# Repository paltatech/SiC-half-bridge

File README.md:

# SiC-half-bridge
Three parallel SiC(Silicon Carbide) Mosfet half bridge

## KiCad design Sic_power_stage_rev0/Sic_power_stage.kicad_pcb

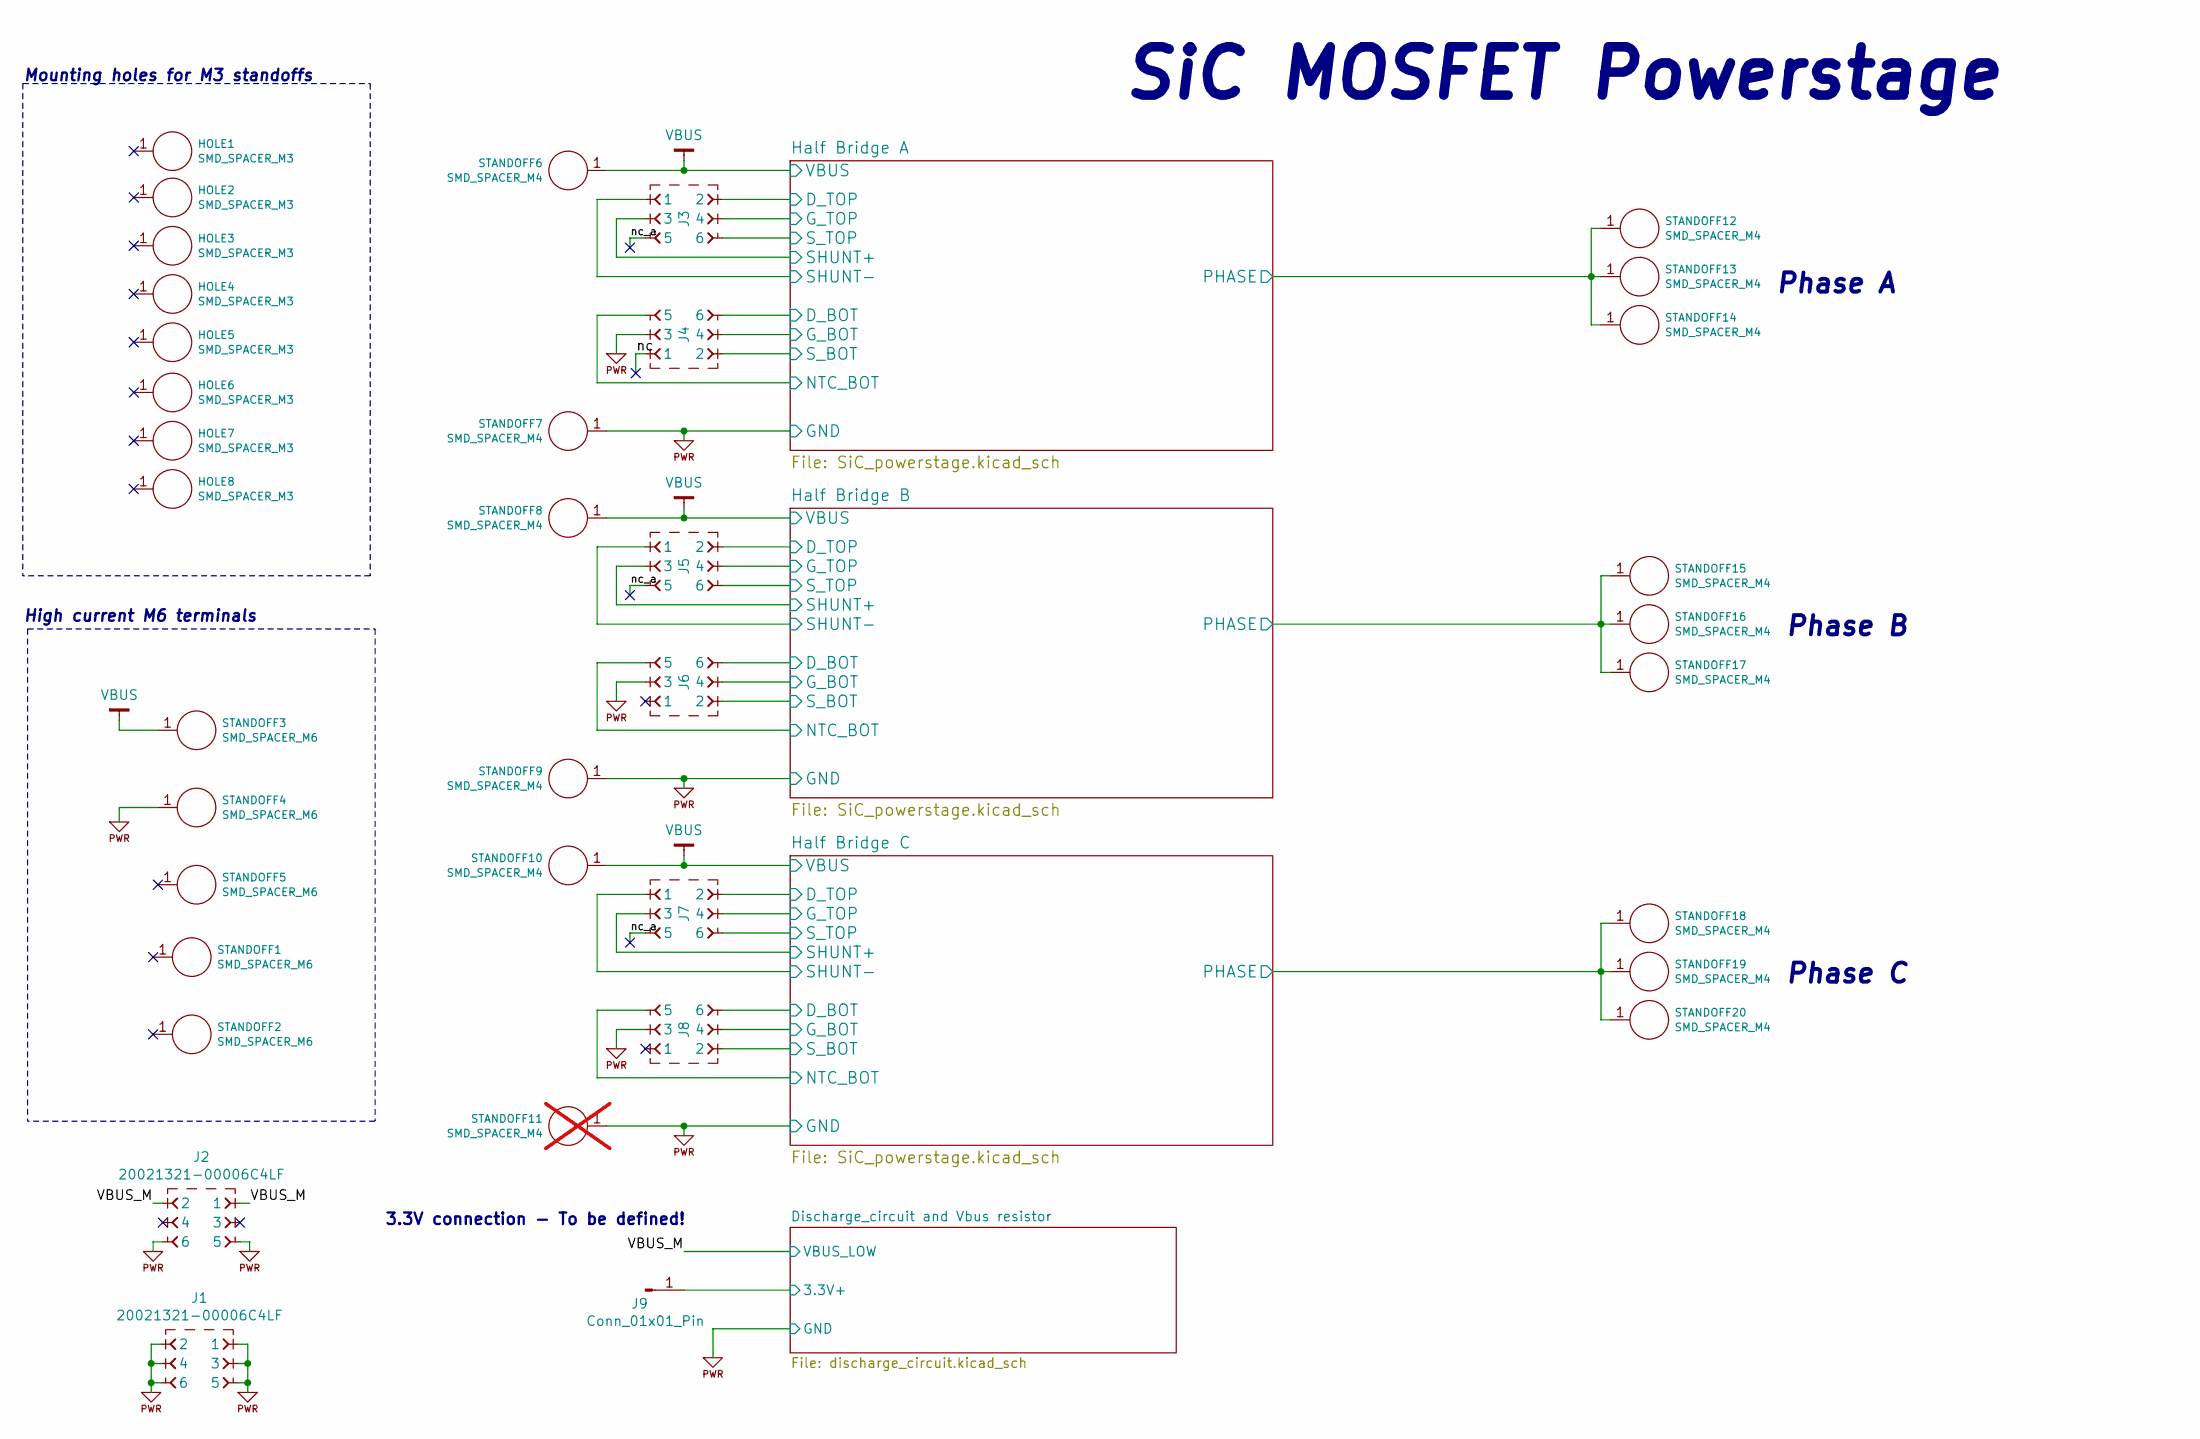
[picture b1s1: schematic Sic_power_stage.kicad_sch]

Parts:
HOLE1, HOLE2, HOLE3, HOLE4, HOLE5, HOLE6, HOLE7, HOLE8: SMD_SPACER_M3; SMTSO-36-6; MPN SMTSO-36-60-MTJ
J1, J2, J3, J4, J5, J6, J7, J8: 20021321-00006C4LF; CONN-20021321-00006C4LF-no-hole; MPN 20021321-00006C4LF
J9: Conn_01x01_Pin; PinHeader_1x01_P1.00mm_Vertical
STANDOFF1, STANDOFF2, STANDOFF3, STANDOFF4, STANDOFF5: SMD_SPACER_M6; Standoff_M4; MPN Brass Inserts(M6*8*12)
STANDOFF6, STANDOFF7, STANDOFF8, STANDOFF9, STANDOFF10, STANDOFF12, STANDOFF13, STANDOFF14, STANDOFF15, STANDOFF16, STANDOFF17, STANDOFF18, STANDOFF19, STANDOFF20: SMD_SPACER_M4; Standoff_M4; MPN SMTSO-40-120-M-T-S
STANDOFF11: SMD_SPACER_M4; Standoff_M4; MPN SMTSO-40-120-M-T-S; not fitted

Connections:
/Discharge_circuit and Vbus resistor/3.3V+: J9.1; also elsewhere on the board
/Half Bridge A/D_BOT: J4.6; also elsewhere on the board
/Half Bridge A/D_TOP: J3.2; also elsewhere on the board
/Half Bridge A/G_BOT: J4.4; also elsewhere on the board
/Half Bridge A/G_TOP: J3.4; also elsewhere on the board
/Half Bridge A/NTC_BOT: J4.5; also elsewhere on the board
/Half Bridge A/PHASE: STANDOFF12.1, STANDOFF13.1, STANDOFF14.1; also elsewhere on the board
/Half Bridge A/SHUNT+: J3.3; also elsewhere on the board
/Half Bridge A/SHUNT-: J3.1; also elsewhere on the board
/Half Bridge A/S_BOT: J4.2; also elsewhere on the board
/Half Bridge A/S_TOP: J3.6; also elsewhere on the board
/Half Bridge B/D_BOT: J6.6; also elsewhere on the board
/Half Bridge B/D_TOP: J5.2; also elsewhere on the board
/Half Bridge B/G_BOT: J6.4; also elsewhere on the board
/Half Bridge B/G_TOP: J5.4; also elsewhere on the board
/Half Bridge B/NTC_BOT: J6.5; also elsewhere on the board
/Half Bridge B/PHASE: STANDOFF15.1, STANDOFF16.1, STANDOFF17.1; also elsewhere on the board
/Half Bridge B/SHUNT+: J5.3; also elsewhere on the board
/Half Bridge B/SHUNT-: J5.1; also elsewhere on the board
/Half Bridge B/S_BOT: J6.2; also elsewhere on the board
/Half Bridge B/S_TOP: J5.6; also elsewhere on the board
/Half Bridge C/D_BOT: J8.6; also elsewhere on the board
/Half Bridge C/D_TOP: J7.2; also elsewhere on the board
/Half Bridge C/G_BOT: J8.4; also elsewhere on the board
/Half Bridge C/G_TOP: J7.4; also elsewhere on the board
/Half Bridge C/NTC_BOT: J8.5; also elsewhere on the board
/Half Bridge C/PHASE: STANDOFF18.1, STANDOFF19.1, STANDOFF20.1; also elsewhere on the board
/Half Bridge C/SHUNT+: J7.3; also elsewhere on the board
/Half Bridge C/SHUNT-: J7.1; also elsewhere on the board
/Half Bridge C/S_BOT: J8.2; also elsewhere on the board
/Half Bridge C/S_TOP: J7.6; also elsewhere on the board
/VBUS_M: J2.1, J2.2; also elsewhere on the board
/nc: J4.1
/nc_a: J3.5, J5.5, J7.5
PWRGND: J1.1, J1.2, J1.3, J1.4, J1.5, J1.6, J2.5, J2.6, J4.3, J6.3, J8.3, STANDOFF4.1, STANDOFF7.1, STANDOFF9.1, STANDOFF11.1; also elsewhere on the board
VBUS: STANDOFF3.1, STANDOFF6.1, STANDOFF8.1, STANDOFF10.1; also elsewhere on the board

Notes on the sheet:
High current M6 terminals
Mounting holes for M3 standoffs
Phase B
Phase A
Phase C
3.3V connection - To be defined!
SiC MOSFET Powerstage

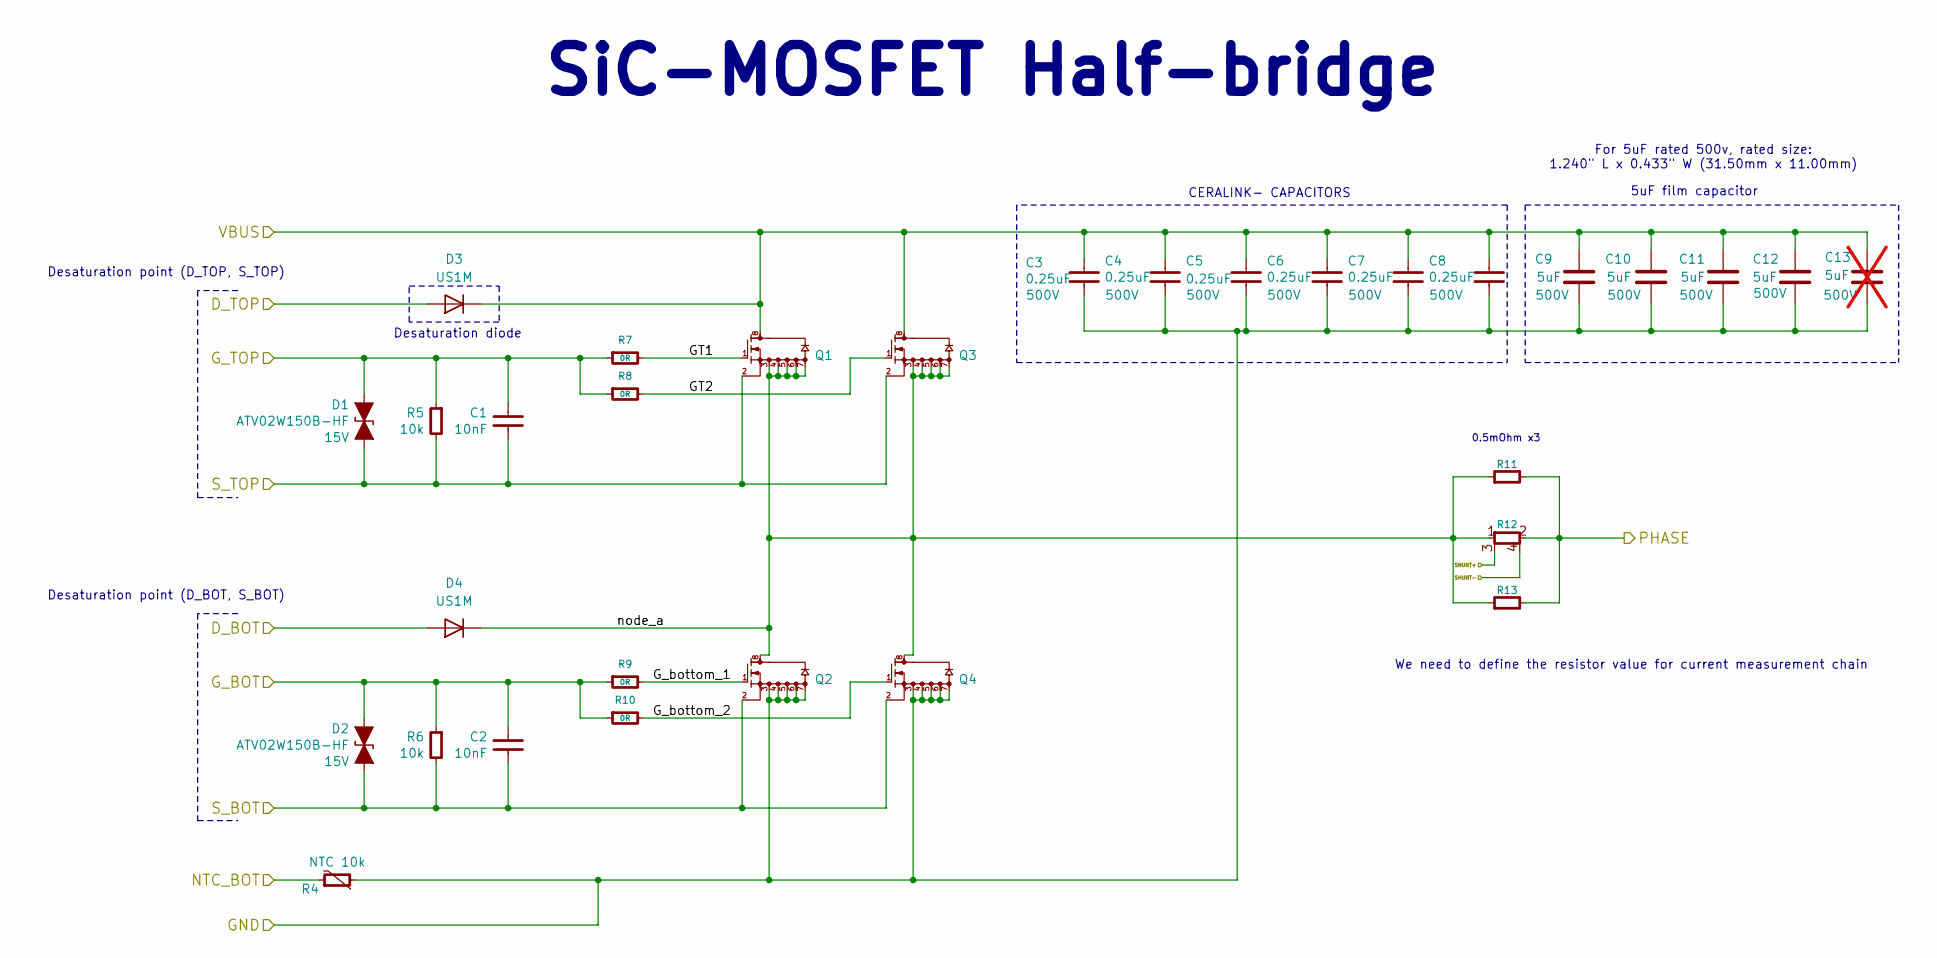
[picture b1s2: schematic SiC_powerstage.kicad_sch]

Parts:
C1, C2: 10nF; CAPC1608X55; Voltage 50V; MPN C1608X7R1H103K080AA
C3: 0.25uF; CAPC5750X279; MPN B58043I5254M052
C4, C5, C6, C7, C8: 0.25uF; CAPC5750X279; Voltage 500V; MPN B58043I5254M052
C9, C10, C11, C12: 5uF; C_Rect_L31.5mm_W11.0mm_P27.50mm_MKS4; Voltage 500V; MPN B32714H5505K000
C13: 5uF; C_Rect_L18.0mm_W9.0mm_P15.00mm_FKS3_FKP3; Voltage 500V; MPN B32714H5505K000; not fitted
D1, D2: ATV02W150B-HF; SOD-123F; Voltage 15V; MPN ATV02W150B-HF
D3, D4: US1M; D_SMA
Q1, Q2, Q3, Q4: NTBG014N120M3P; TO-263-7_TabPin8; MPN NTBG014N120M3P; LCSC Part # C5209029
R4: NTC 10k; RESC1608X50; MPN NCU18XH103F60RB
R5, R6: 10k; RESC1608X50; MPN AC0603FR-0710KL
R7, R8, R9, R10: 0R; RESC1608X50; MPN RMCF0603ZT0R00
R11, R13: 500UOhm; VISHAY-WSL3921L5000FEA; MPN WSLP3921L5000FEA
R12: 500UOhm; WSL3921L5000FEA; MPN WSLP3921L5000FEA

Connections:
/Half Bridge A/D_BOT: D4.2 (A); also elsewhere on the board
/Half Bridge A/D_TOP: D3.2 (A); also elsewhere on the board
/Half Bridge A/GT1: Q1.1, R7.2
/Half Bridge A/GT2: Q3.1, R8.2
/Half Bridge A/G_BOT: C2.1, D2.1 (A1), R6.1, R9.1, R10.1; also elsewhere on the board
/Half Bridge A/G_TOP: C1.1, D1.1 (A1), R5.1, R7.1, R8.1; also elsewhere on the board
/Half Bridge A/G_bottom_1: Q2.1, R9.2
/Half Bridge A/G_bottom_2: Q4.1, R10.2
/Half Bridge A/NTC_BOT: R4.1; also elsewhere on the board
/Half Bridge A/PHASE: R11.2, R12.2, R13.2; also elsewhere on the board
/Half Bridge A/SHUNT+: R12.3; also elsewhere on the board
/Half Bridge A/SHUNT-: R12.4; also elsewhere on the board
/Half Bridge A/S_BOT: C2.2, D2.2 (A2), Q2.2, Q4.2, R6.2; also elsewhere on the board
/Half Bridge A/S_TOP: C1.2, D1.2 (A2), Q1.2, Q3.2, R5.2; also elsewhere on the board
/Half Bridge A/node_a: D4.1 (K), Q1.3, Q1.4, Q1.5, Q1.6, Q1.7, Q2.8, Q3.3, Q3.4, Q3.5, Q3.6, Q3.7, Q4.8, R11.1, R12.1, R13.1
PWRGND: C3.2, C4.2, C5.2, C6.2, C7.2, C8.2, C9.2, C10.2, C11.2, C12.2, C13.2, Q2.3, Q2.4, Q2.5, Q2.6, Q2.7, Q4.3, Q4.4, Q4.5, Q4.6, Q4.7, R4.2; also elsewhere on the board
VBUS: C3.1, C4.1, C5.1, C6.1, C7.1, C8.1, C9.1, C10.1, C11.1, C12.1, C13.1, D3.1 (K), Q1.8, Q3.8; also elsewhere on the board

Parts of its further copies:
C14, C15, C27, C28: 10nF; CAPC1608X55; Voltage 50V; MPN C1608X7R1H103K080AA
C16, C29: 0.25uF; CAPC5750X279; MPN B58043I5254M052
C17, C18, C19, C20, C21, C30, C31, C32, C33, C34: 0.25uF; CAPC5750X279; Voltage 500V; MPN B58043I5254M052
C22, C23, C24, C25, C35, C36, C37, C38: 5uF; C_Rect_L31.5mm_W11.0mm_P27.50mm_MKS4; Voltage 500V; MPN B32714H5505K000
D5, D6, D9, D10: ATV02W150B-HF; SOD-123F; Voltage 15V; MPN ATV02W150B-HF
D7, D8, D11, D12: US1M; D_SMA
Q5, Q6, Q7, Q8, Q9, Q10, Q11, Q12: NTBG014N120M3P; TO-263-7_TabPin8; MPN NTBG014N120M3P; LCSC Part # C5209029
R14, R24: NTC 10k; RESC1608X50; MPN NCU18XH103F60RB
R15, R16, R25, R26: 10k; RESC1608X50; MPN AC0603FR-0710KL
R17, R18, R19, R20, R27, R28, R29, R30: 0R; RESC1608X50; MPN RMCF0603ZT0R00
R21, R23, R31, R33: 500UOhm; VISHAY-WSL3921L5000FEA; MPN WSLP3921L5000FEA
R22, R32: 500UOhm; WSL3921L5000FEA; MPN WSLP3921L5000FEA

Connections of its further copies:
/Half Bridge B/D_BOT: D8.2 (A); also elsewhere on the board
/Half Bridge B/D_TOP: D7.2 (A); also elsewhere on the board
/Half Bridge B/GT1: Q5.1, R17.2
/Half Bridge B/GT2: Q7.1, R18.2
/Half Bridge B/G_BOT: C15.1, D6.1 (A1), R16.1, R19.1, R20.1; also elsewhere on the board
/Half Bridge B/G_TOP: C14.1, D5.1 (A1), R15.1, R17.1, R18.1; also elsewhere on the board
/Half Bridge B/G_bottom_1: Q6.1, R19.2
/Half Bridge B/G_bottom_2: Q8.1, R20.2
/Half Bridge B/NTC_BOT: R14.1; also elsewhere on the board
/Half Bridge B/PHASE: R21.2, R22.2, R23.2; also elsewhere on the board
/Half Bridge B/SHUNT+: R22.3; also elsewhere on the board
/Half Bridge B/SHUNT-: R22.4; also elsewhere on the board
/Half Bridge B/S_BOT: C15.2, D6.2 (A2), Q6.2, Q8.2, R16.2; also elsewhere on the board
/Half Bridge B/S_TOP: C14.2, D5.2 (A2), Q5.2, Q7.2, R15.2; also elsewhere on the board
/Half Bridge B/node_a: D8.1 (K), Q5.3, Q5.4, Q5.5, Q5.6, Q5.7, Q6.8, Q7.3, Q7.4, Q7.5, Q7.6, Q7.7, Q8.8, R21.1, R22.1, R23.1
/Half Bridge C/D_BOT: D12.2 (A); also elsewhere on the board
/Half Bridge C/D_TOP: D11.2 (A); also elsewhere on the board
/Half Bridge C/GT1: Q9.1, R27.2
/Half Bridge C/GT2: Q11.1, R28.2
/Half Bridge C/G_BOT: C28.1, D10.1 (A1), R26.1, R29.1, R30.1; also elsewhere on the board
/Half Bridge C/G_TOP: C27.1, D9.1 (A1), R25.1, R27.1, R28.1; also elsewhere on the board
/Half Bridge C/G_bottom_1: Q10.1, R29.2
/Half Bridge C/G_bottom_2: Q12.1, R30.2
/Half Bridge C/NTC_BOT: R24.1; also elsewhere on the board
/Half Bridge C/PHASE: R31.2, R32.2, R33.2; also elsewhere on the board
/Half Bridge C/SHUNT+: R32.3; also elsewhere on the board
/Half Bridge C/SHUNT-: R32.4; also elsewhere on the board
/Half Bridge C/S_BOT: C28.2, D10.2 (A2), Q10.2, Q12.2, R26.2; also elsewhere on the board
/Half Bridge C/S_TOP: C27.2, D9.2 (A2), Q9.2, Q11.2, R25.2; also elsewhere on the board
/Half Bridge C/node_a: D12.1 (K), Q9.3, Q9.4, Q9.5, Q9.6, Q9.7, Q10.8, Q11.3, Q11.4, Q11.5, Q11.6, Q11.7, Q12.8, R31.1, R32.1, R33.1
PWRGND: C16.2, C17.2, C18.2, C19.2, C20.2, C21.2, C22.2, C23.2, C24.2, C25.2, C29.2, C30.2, C31.2, C32.2, C33.2, C34.2, C35.2, C36.2, C37.2, C38.2, Q6.3, Q6.4, Q6.5, Q6.6, Q6.7, Q8.3, Q8.4, Q8.5, Q8.6, Q8.7, Q10.3, Q10.4, Q10.5, Q10.6, Q10.7, Q12.3, Q12.4, Q12.5, Q12.6, Q12.7, R14.2, R24.2; also elsewhere on the board
VBUS: C16.1, C17.1, C18.1, C19.1, C20.1, C21.1, C22.1, C23.1, C24.1, C25.1, C29.1, C30.1, C31.1, C32.1, C33.1, C34.1, C35.1, C36.1, C37.1, C38.1, D7.1 (K), D11.1 (K), Q5.8, Q7.8, Q9.8, Q11.8; also elsewhere on the board

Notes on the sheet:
Desaturation point (D_BOT, S_BOT)
We need to define the resistor value for current measurement chain
Desaturation point (D_TOP, S_TOP)
SiC-MOSFET Half-bridge
For 5uF rated 500v, rated size: 1.240" L x 0.433" W (31.50mm x 11.00mm)
Desaturation diode
5uF film capacitor
CERALINK- CAPACITORS
0.5mOhm x3

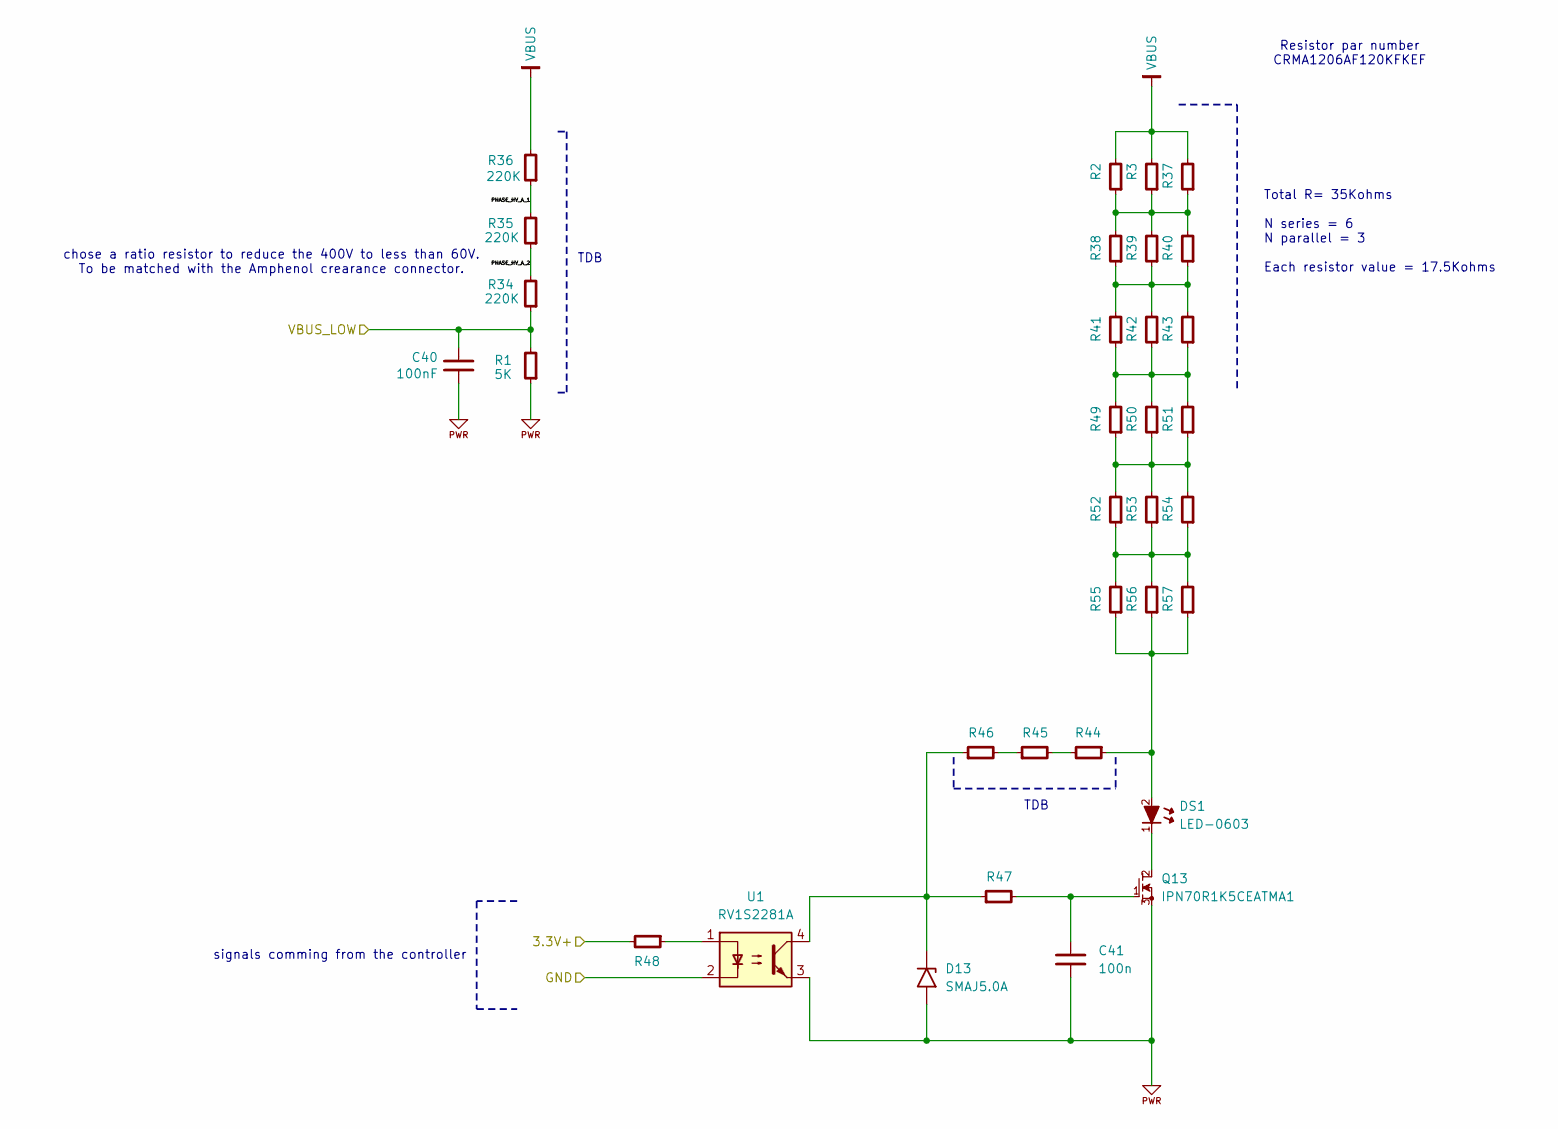
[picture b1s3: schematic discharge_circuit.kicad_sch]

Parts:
C40: 100nF; CAPC1608X55; Voltage 50V; MPN C1608X7R1H103K080AA
C41: 100n; CAPC1608X55
D13: SMAJ5.0A; D_SMA
DS1: LED-0603
Q13: IPN70R1K5CEATMA1; SOT-223-3
R1: 5K; R_0603_1608Metric
R2, R3, R37, R38, R39, R40, R41, R42, R43, R49, R50, R51, R52, R53, R54, R55, R56, R57: 17.6K; RESC3216X60; MPN RNCF1206BKE17K6
R34, R35, R36: 220K; RESC3216X60
R44, R45, R46: 365K; RESC3216X60; MPN CRCW1206365KFKEA
R47: 10R; R_0805_2012Metric; MPN CRCW080510R0FKEA
R48: R-1206; R_0603_1608Metric
U1: RV1S2281A; SSOP-4_4.4x2.6mm_P1.27mm; MPN RV1S2281ACCSP-10YC#SC0

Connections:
/Discharge_circuit and Vbus resistor/3.3V+: R48.2; also elsewhere on the board
/Discharge_circuit and Vbus resistor/PHASE_HV_A_1: R35.2, R36.1
/Discharge_circuit and Vbus resistor/PHASE_HV_A_2: R34.2, R35.1
/VBUS_M: C40.1, R1.2, R34.1; also elsewhere on the board
unnamed: D13.1 (A1), R46.1, R47.1, U1.4
unnamed: DS1.2 (A), R44.1, R55.1, R56.1, R57.1
unnamed: DS1.1 (K), Q13.2 (S)
unnamed: C41.1, Q13.1 (G), R47.2
unnamed: R2.1, R3.1, R37.1, R38.2, R39.2, R40.2
unnamed: R38.1, R39.1, R40.1, R41.2, R42.2, R43.2
unnamed: R41.1, R42.1, R43.1, R49.2, R50.2, R51.2
unnamed: R44.2, R45.2
unnamed: R45.1, R46.2
unnamed: R48.1, U1.1
unnamed: R49.1, R50.1, R51.1, R52.2, R53.2, R54.2
unnamed: R52.1, R53.1, R54.1, R55.2, R56.2, R57.2
PWRGND: C40.2, C41.2, D13.2 (A2), Q13.3 (D), R1.1, U1.2, U1.3; also elsewhere on the board
VBUS: R2.2, R3.2, R36.2, R37.2; also elsewhere on the board

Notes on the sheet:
Resistor par number CRMA1206AF120KFKEF
TDB
signals comming from the controller
Total R= 35Kohms N series = 6 N parallel = 3 Each resistor value = 17.5Kohms
chose a ratio resistor to reduce the 400V to less than 60V. To be matched with the Amphenol crearance connector.

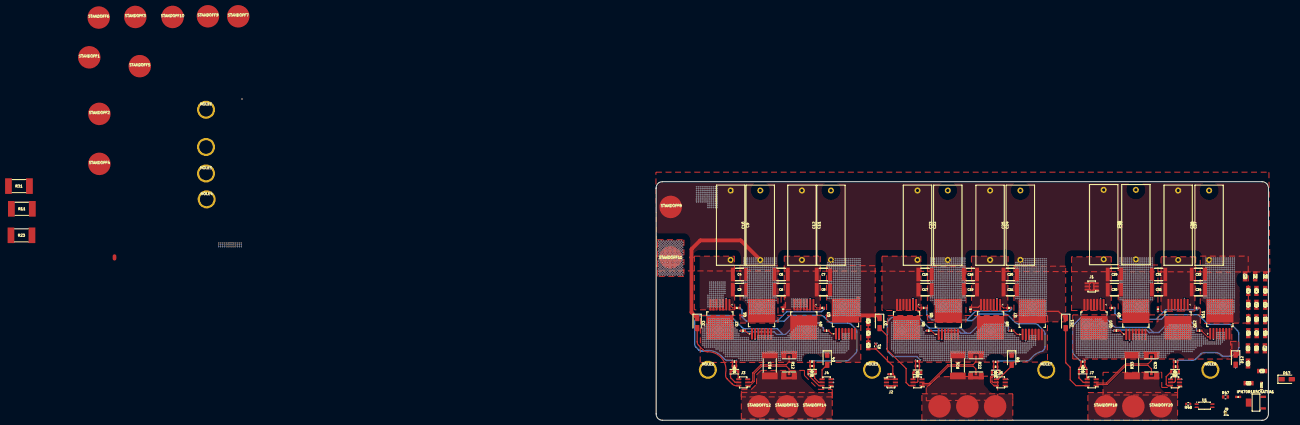
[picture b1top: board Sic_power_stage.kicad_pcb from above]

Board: 4 copper layers, 242.5 x 94.5 mm, 160 parts (0 on the bottom side), 64 nets.

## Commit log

2024-09-26 First design attempt in progress.
2024-10-01 Add inner tracks, define layers and add some changes
2024-11-07 WIP: define custom rules, change inner layer PWRGND , VBUS
2024-11-13 Increase clearance between mosfets, Add alternating film capacitor
2025-05-19 Move leg A to reduce Cu Area
2025-06-13 Add changes in power stage
    - Redefine DC-link capacitor size per leg.
    - Change footprint SiC MOSFET.
2025-06-16 Define Ceralink capacitor value and qty
2025-06-17 Add changes
    - Add DC-LINK capacitor discharge circuit.
    - VBUS resistive divider.
2025-06-30 Changes Added
    - Define DC-LINK capacitors position.
    - Redefine layout in phase A.
    - Place Mosfet Leg B, (need to be placed simetrical).
2025-07-02 Define custom rules
2025-08-05 Redefine SiC layout
2025-08-06 Add minor changes
2025-09-21 Re allocate film capacitors and re define layout for power mosfet
2025-10-27 Add traces for leg A referring to gate and driver source
2025-10-29 Add tentative routing for leg A
2025-10-30 Add traces for LEG-A, tentative place for main power supply
2025-12-17 SiC: routing phase A and B - place components
2025-12-18 SiC: modify routing in leg A - Change footprint for Amphenol connector
2025-12-18 SiC: finish routing on leg B
2025-12-18 SiC: define routing for leg C
2025-12-22 Sic: change layer for gate and driver source
2025-12-22 Sic: finish leg C
2025-12-22 Sic: Change track shape for NTC leg C
2025-12-22 Sic: Define route for SHUNT leg C
2025-12-22 Sic: Increase copper area for thermal dissipation
2025-12-22 Sic: Add more vias on Leg A
2026-01-07 Sic: Add vias on leg B
2026-01-07 Sic: Add vias on leg C
2026-01-07 Sic: Vias on Led C - Vbus
2026-01-08 Sic: define resistors value for discharge circuit
2026-01-13 Sic: Define custom rules for Vbus sense
2026-01-14 SiC: Change DC-LINK MLCC capacitor
    - Originally, the estimation about the ceramic capacitor value was 0.25uF. This is for CERALINK capacitor as the DC-BIAS
    affects its capacitance just 1% for 400V. Now a MLCC was chosen, and the DC-BIAS is into account for this application
    would be great to test with both capacitors and check the bahaviour between them.
